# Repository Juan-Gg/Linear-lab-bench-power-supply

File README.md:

# Linear-lab-bench-power-supply
This is a dual channel linear lab power supply, each channel capable of 30 V at 500 mA.
More information here: https://juangg-projects.blogspot.com/2019/05/linear-lab-power-supply.html

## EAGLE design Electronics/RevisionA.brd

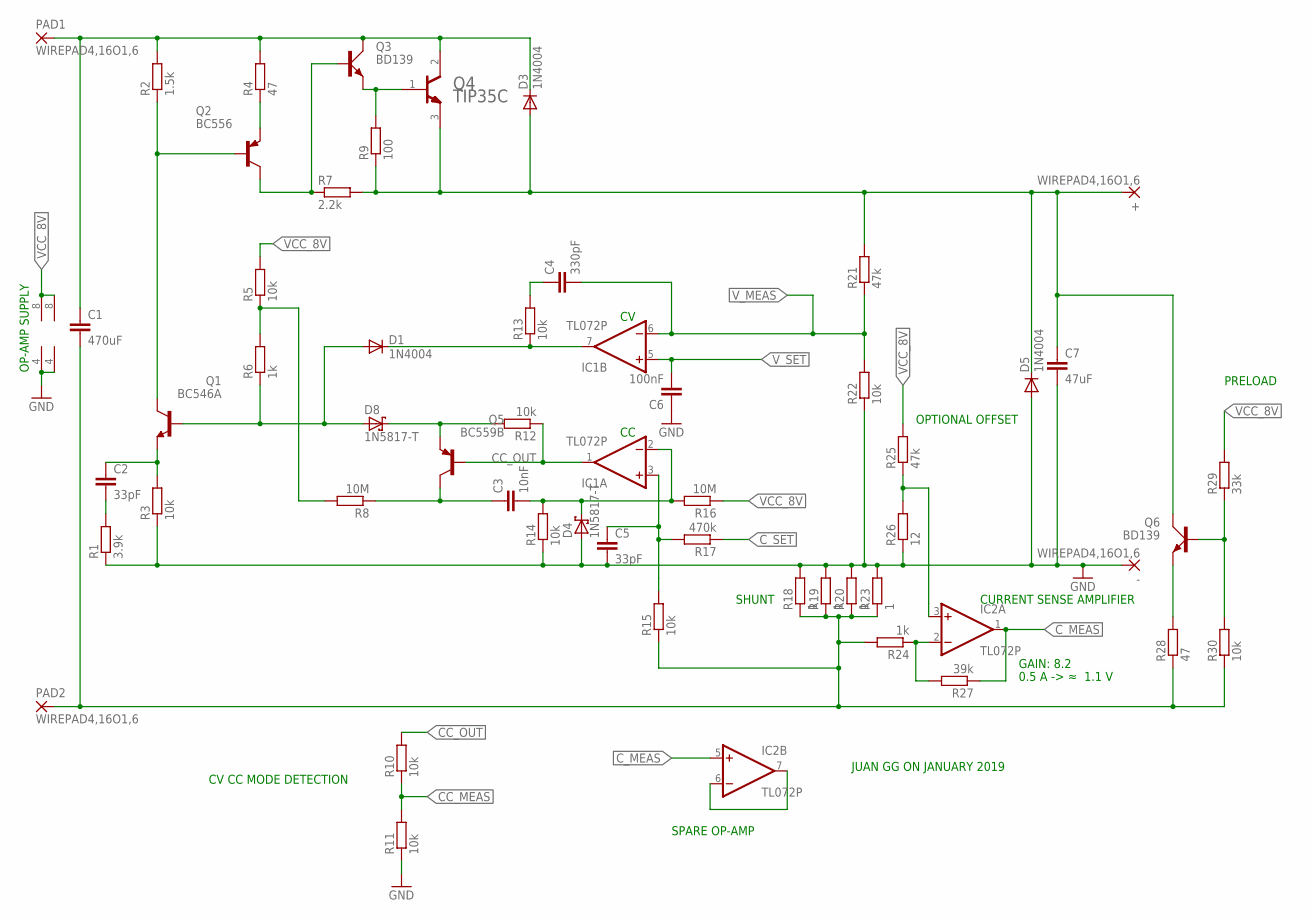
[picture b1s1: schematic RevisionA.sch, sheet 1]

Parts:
+: WIREPAD4,16O1,6; 4,16O1,6
-: WIREPAD4,16O1,6; 4,16O1,6
C1: 470uF; C5B7.2
C2, C5: 33pF; C2.5-2
C3: 10nF; C2.5-2
C4: 330pF; C2.5-2
C6: 100nF; C2.5-2
C7: 47uF; C5B7.2
D1, D3, D5: 1N4004; DO41-10
D4, D8: 1N5817-T; DO41-7.6
IC1, IC2: TL072P; DIL08
PAD1, PAD2: WIREPAD4,16O1,6; 4,16O1,6
Q1: BC546A; TO92-EBC
Q2: BC556; TO92-EBC
Q3, Q6: BD139; TO126AV
Q4: STMICROELECTRONICS_TIP35CSTMICROELECTRONICS_TIP35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; STMICROELECTRONICS_TIP35C_0
Q5: BC559B; TO92-EBC
R1: 3.9k; 0207/10
R2: 1.5k; 0207/10
R3, R5, R10, R11, R12, R13, R14, R15, R22, R30: 10k; 0207/10
R4, R28: 47; 0207/10
R6, R24: 1k; 0207/10
R7: 2.2k; 0207/10
R8, R16: 10M; 0207/10
R9: 100; 0207/10
R17: 470k; 0207/10
R18, R19, R20, R23: 1; 0617V
R21, R25: 47k; 0207/10
R26: 12; 0207/10
R27: 39k; 0207/10
R29: 33k; 0207/10

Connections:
+UNREG(MAIN): C1.1, D3.C, PAD1.1, Q3.C, Q4.2 (COLLECTOR), R2.2, R4.2
-UNREG(MAIN): C1.2, PAD2.1, R15.1, R18.1, R19.1, R20.1, R23.1, R24.2, R28.1, R30.1
CC_MEAS: R10.1, R11.2; also elsewhere on the board
CC_OUT: IC1.1 (OUT), Q5.B, R10.2, R12.1
C_MEAS: IC2.1 (OUT), IC2.5 (+IN), R27.1; also elsewhere on the board
C_SET: R17.1; also elsewhere on the board
GND: -.1, C5.2, C6.1, C7.2, D4.A, D5.A, IC1.4 (V-), IC2.4 (V-), R1.1, R3.1, R11.1, R14.1, R18.2, R19.2, R20.2, R22.1, R23.2, R26.1; also elsewhere on the board
unnamed: Q3.E, Q4.1 (BASE), R9.2
unnamed: +.1, C7.1, D3.A, D5.C, Q4.3 (EMITTER), Q6.C, R7.2, R9.1, R21.2
unnamed: Q2.C, Q3.B, R7.1
unnamed: Q2.E, R4.1
unnamed: Q1.C, Q2.B, R2.1
unnamed: R5.1, R6.2, R8.2
unnamed: D1.A, D8.A, Q1.B, R6.1
unnamed: C2.1, Q1.E, R3.2
unnamed: C2.2, R1.2
unnamed: D8.C, Q5.E, R12.2
unnamed: C3.2, D4.C, IC1.2 (-IN), R14.2, R16.2
unnamed: C3.1, Q5.C, R8.1
unnamed: C5.1, IC1.3 (+IN), R15.2, R17.2
unnamed: D1.C, IC1.7 (OUT), R13.1
unnamed: C4.1, R13.2
unnamed: Q6.E, R28.2
unnamed: Q6.B, R29.1, R30.2
unnamed: IC2.2 (-IN), R24.1, R27.2
unnamed: IC2.6 (-IN), IC2.7 (OUT)
unnamed: IC2.3 (+IN), R25.1, R26.2
VCC_8V: IC1.8 (V+), IC2.8 (V+), R5.2, R16.1, R25.2, R29.2; also elsewhere on the board
V_MEAS: C4.2, IC1.6 (-IN), R21.1, R22.2; also elsewhere on the board
V_SET: C6.2, IC1.5 (+IN); also elsewhere on the board

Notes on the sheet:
GAIN: 8.2
OPTIONAL OFFSET
SPARE OP-AMP
0.5 A -> ≈ 1.1 V
PRELOAD
CV CC MODE DETECTION
OP-AMP SUPPLY
CURRENT SENSE AMPLIFIER
SHUNT
JUAN GG ON JANUARY 2019

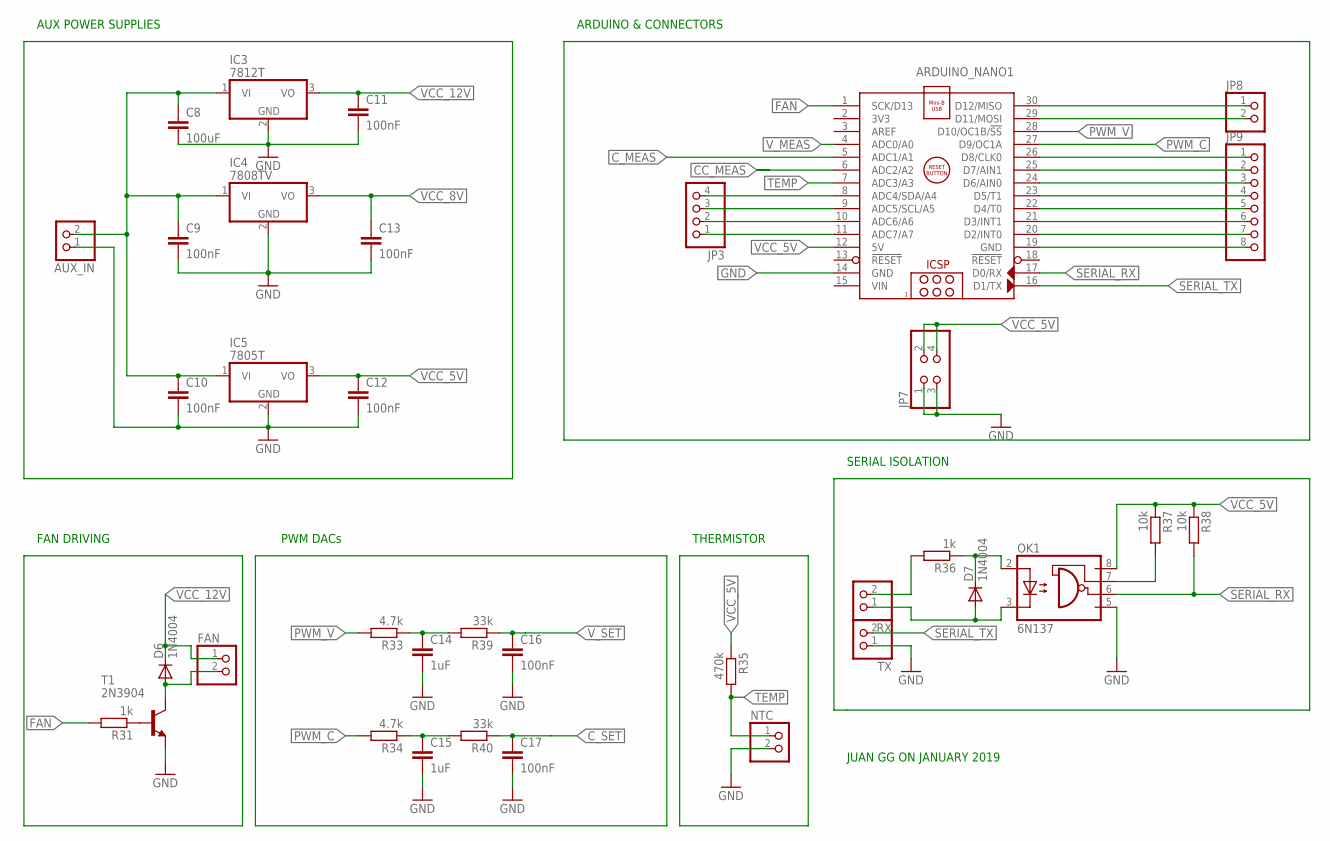
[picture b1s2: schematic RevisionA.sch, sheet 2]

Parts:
ARDUINO_NANO1: ARDUINO_NANO
AUX_IN: PINHD-1X2; 1X02
C8: 100uF; C2.5-4
C9, C10, C11, C12, C13: 100nF; C2.5-2
C14, C15: 1uF; C2.5-4
C16, C17: 100nF; C2.5-4
D6, D7: 1N4004; DO41-10
FAN: PINHD-1X2; 1X02
IC3: 7812T; TO220H
IC4: 7808TV; TO220H
IC5: 7805T; TO220H
JP3: PINHD-1X4; 1X04
JP7: PINHD-2X2; 2X02
JP8: PINHD-1X2; 1X02
JP9: PINHD-1X8; 1X08
NTC: PINHD-1X2; 1X02
OK1: 6N137; DIL08
R31, R36: 1k; 0207/10
R33, R34: 4.7k; 0207/10
R35: 470k; 0207/10
R37, R38: 10k; 0207/10
R39, R40: 33k; 0207/10
RX: PINHD-1X2; 1X02
T1: 2N3904; TO92
TX: PINHD-1X2; 1X02

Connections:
+UNREG(AUX): AUX_IN.2, C8.1, C9.1, C10.1, IC3.1 (VI), IC4.1 (VI), IC5.1 (VI)
A6: ARDUINO_NANO1.10 (ADC6/A6), JP3.2
A7: ARDUINO_NANO1.11 (ADC7/A7), JP3.1
CC_MEAS: ARDUINO_NANO1.6 (ADC2/A2); also elsewhere on the board
C_MEAS: ARDUINO_NANO1.5 (ADC1/A1); also elsewhere on the board
C_SET: C17.1, R40.1; also elsewhere on the board
D2: ARDUINO_NANO1.20 (D2/INT0), JP9.7
D3: ARDUINO_NANO1.21 (D3/INT1), JP9.6
D4: ARDUINO_NANO1.22 (D4/T0), JP9.5
D5: ARDUINO_NANO1.23 (D5/T1), JP9.4
D6: ARDUINO_NANO1.24 (D6/AIN0), JP9.3
D7: ARDUINO_NANO1.25 (D7/AIN1), JP9.2
D8: ARDUINO_NANO1.26 (D8/CLK0), JP9.1
D11: ARDUINO_NANO1.29 (D11/MOSI), JP8.2
D12: ARDUINO_NANO1.30 (D12/MISO), JP8.1
FAN: ARDUINO_NANO1.1 (SCK/D13), R31.2
GND: ARDUINO_NANO1.14 (GND), ARDUINO_NANO1.19 (GND), AUX_IN.1, C8.2, C9.2, C10.2, C11.2, C12.2, C13.2, C14.2, C15.2, C16.2, C17.2, IC3.2 (GND), IC4.2 (GND), IC5.2 (GND), JP7.1, JP7.3, JP9.8, NTC.2, OK1.5 (GND), T1.3 (E), TX.1; also elsewhere on the board
unnamed: D7.C, OK1.2 (A), R36.1
unnamed: C14.1, R33.1, R39.2
unnamed: OK1.7 (VE), R37.2
unnamed: D6.A, FAN.2, T1.1 (C)
unnamed: R31.1, T1.2 (B)
unnamed: C15.1, R34.1, R40.2
unnamed: R36.2, RX.2
unnamed: D7.A, OK1.3 (C), RX.1
unnamed: ARDUINO_NANO1.8 (ADC4/SDA/A4), JP3.4
unnamed: ARDUINO_NANO1.9 (ADC5/SCL/A5), JP3.3
PWM_C: ARDUINO_NANO1.27 (D9/OC1A), R34.2
PWM_V: ARDUINO_NANO1.28 (D10/OC1B/!SS), R33.2
SERIAL_RX: ARDUINO_NANO1.17 (D0/RX), OK1.6 (VO), R38.2
SERIAL_TX: ARDUINO_NANO1.16 (D1/TX), TX.2
TEMP: ARDUINO_NANO1.7 (ADC3/A3), NTC.1, R35.2
VCC_5V: ARDUINO_NANO1.12 (5V), C12.1, IC5.3 (VO), JP7.2, JP7.4, OK1.8 (VCC), R35.1, R37.1, R38.1
VCC_8V: C13.1, IC4.3 (VO); also elsewhere on the board
VCC_12V: C11.1, D6.C, FAN.1, IC3.3 (VO)
VIN: ARDUINO_NANO1.15 (VIN)
V_MEAS: ARDUINO_NANO1.4 (ADC0/A0); also elsewhere on the board
V_SET: C16.1, R39.1; also elsewhere on the board

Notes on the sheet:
AUX POWER SUPPLIES
FAN DRIVING
PWM DACs
SERIAL ISOLATION
THERMISTOR
ARDUINO & CONNECTORS
JUAN GG ON JANUARY 2019

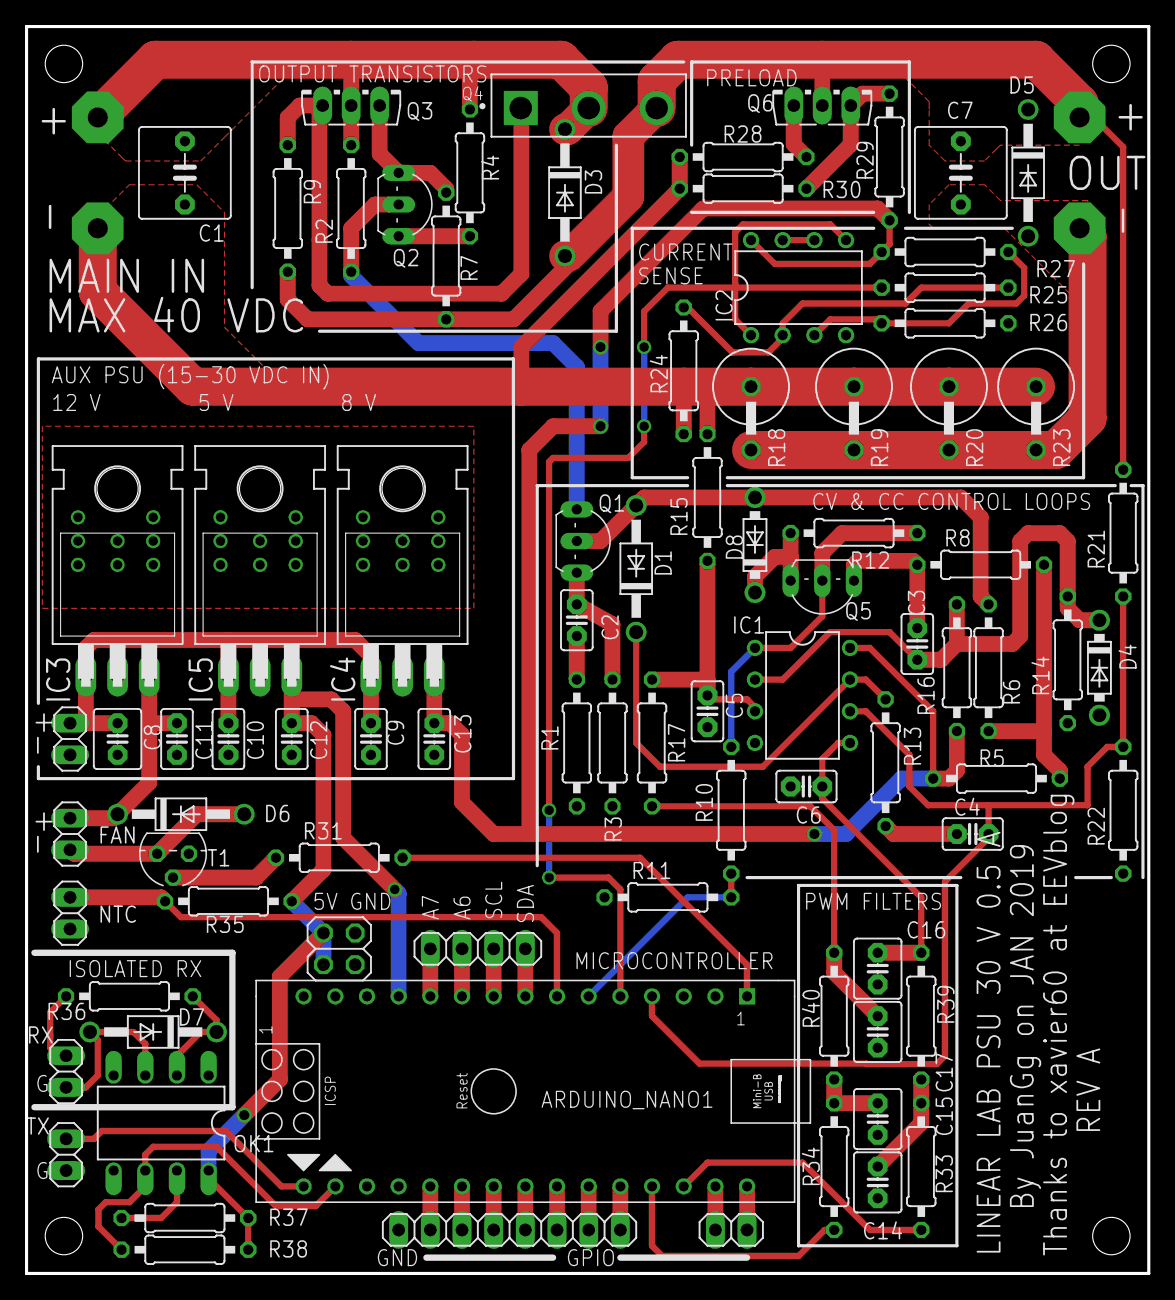
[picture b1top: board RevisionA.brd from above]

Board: 2 copper layers, 90.0 x 100.0 mm, 90 parts (0 on the bottom side), 60 nets.

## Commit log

2019-05-23 Create LICENSE
